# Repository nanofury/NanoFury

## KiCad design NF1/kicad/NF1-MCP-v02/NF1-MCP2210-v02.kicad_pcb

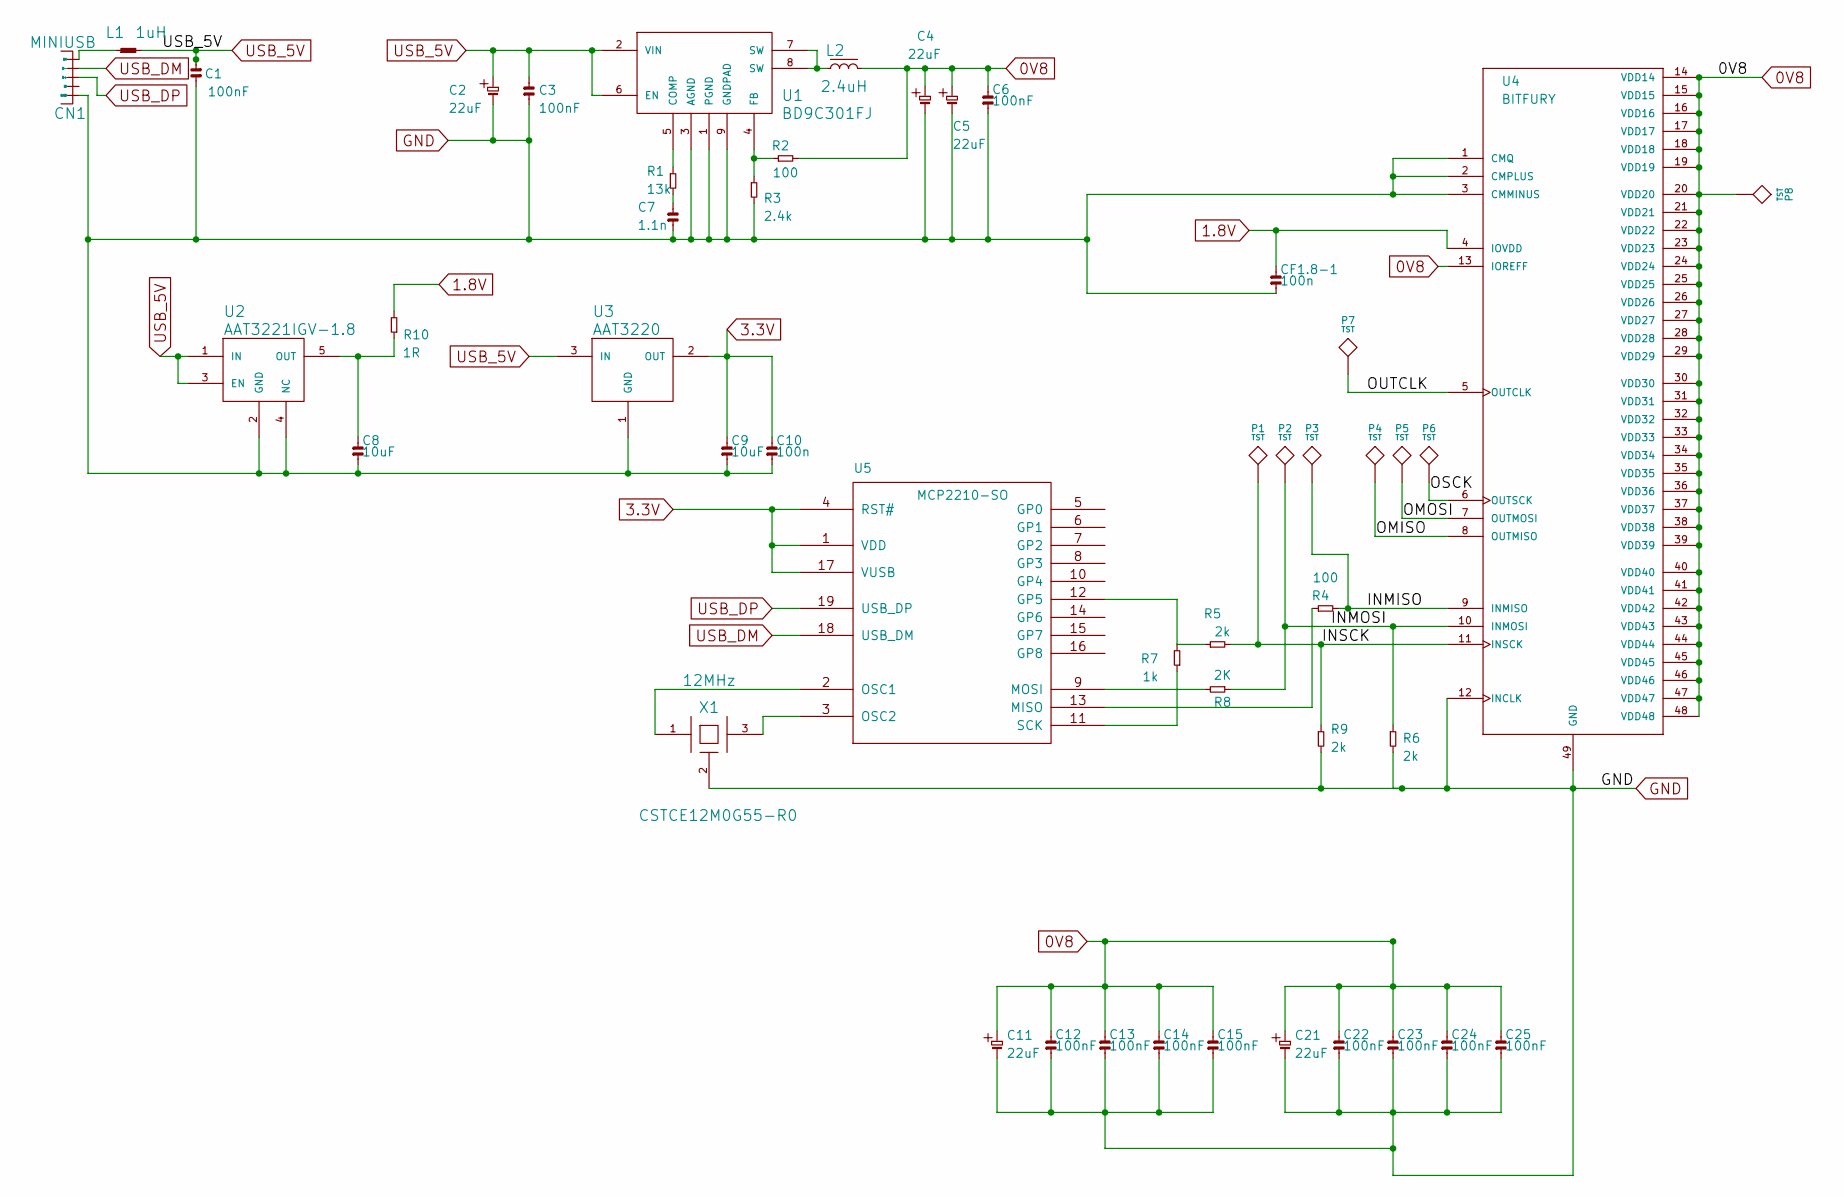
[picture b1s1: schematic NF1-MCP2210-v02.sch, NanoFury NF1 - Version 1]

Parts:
C1, C3, C6, C12, C13, C14, C15, C22, C23, C24, C25: 100nF; 0402
C2, C4, C5, C11, C21: 22uF; 0805
C7: 1.1n; 0402
C8, C9: 10uF; 0805
C10: 100n; 0402
CF1.8-1: 100n; 0402
CN1: MINIUSB; USBAPCB
L1: 1uH; 0402
L2: 2.4uH; 0630
P1, P2, P3, P4, P5, P6, P7, P8: TST; TP
R1: 13k; 0402
R2, R4: 100; 0402
R3: 2.4k; 0402
R5, R6, R9: 2k; 0402
R7: 1k; 0402
R8: 2K; 0402
R10: 1R; 0402
U1: BD9C301FJ; HTSOP-J8
U2: AAT3221IGV-1.8; SOT23-5
U3: AAT3220; SC59
U4: BITFURY; QFN48
U5: MCP2210-SO; SSOP-20
X1: 12MHz; CSTCE_G15C; Part Number CSTCE12M0G55-R0

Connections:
0V8: C4.1, C5.1, C6.1, C11.1, C12.1, C13.1, C14.1, C15.1, C21.1, C22.1, C23.1, C24.1, C25.1, L2.2, P8.1, R2.1, U4.13 (IOREFF), U4.14 (VDD14), U4.15 (VDD15), U4.16 (VDD16), U4.17 (VDD17), U4.18 (VDD18), U4.19 (VDD19), U4.20 (VDD20), U4.21 (VDD21), U4.22 (VDD22), U4.23 (VDD23), U4.24 (VDD24), U4.25 (VDD25), U4.26 (VDD26), U4.27 (VDD27), U4.28 (VDD28), U4.29 (VDD29), U4.30 (VDD30), U4.31 (VDD31), U4.32 (VDD32), U4.33 (VDD33), U4.34 (VDD34), U4.35 (VDD35), U4.36 (VDD36), U4.37 (VDD37), U4.38 (VDD38), U4.39 (VDD39), U4.40 (VDD40), U4.41 (VDD41), U4.42 (VDD42), U4.43 (VDD43), U4.44 (VDD44), U4.45 (VDD45), U4.46 (VDD46), U4.47 (VDD47), U4.48 (VDD48)
1.8V: CF1.8-1.1, R10.1, U4.4 (IOVDD)
3.3V: C9.1, C10.1, U3.2 (OUT), U5.1 (VDD), U5.4 (RST#), U5.17 (VUSB)
/INMISO: P3.1, R4.1, U4.9 (INMISO)
/INMOSI: P2.1, R6.2, R8.2, U4.10 (INMOSI)
/INSCK: P1.1, R5.1, R9.2, U4.11 (INSCK)
/OMISO: P4.1, U4.8 (OUTMISO)
/OMOSI: P5.1, U4.7 (OUTMOSI)
/OSCK: P6.1, U4.6 (OUTSCK)
/OUTCLK: P7.1, U4.5 (OUTCLK)
GND: C1.1, C2.2, C3.2, C4.2, C5.2, C6.2, C7.2, C8.2, C9.2, C10.2, C11.2, C12.2, C13.2, C14.2, C15.2, C21.2, C22.2, C23.2, C24.2, C25.2, CF1.8-1.2, CN1.5 (GND), R3.1, R6.1, R9.1, U1.1 (PGND), U1.3 (AGND), U1.9 (GNDPAD), U2.2 (GND), U2.4 (NC), U3.1 (GND), U4.1 (CMQ), U4.2 (CMPLUS), U4.3 (CMMINUS), U4.12 (INCLK), U4.49 (GND), X1.2 (GND)
unnamed: C7.1, R1.1
unnamed: R1.2, U1.5 (COMP)
unnamed: L2.1, U1.7 (SW), U1.8 (SW)
unnamed: R2.2, R3.2, U1.4 (FB)
unnamed: R7.2, U5.11 (SCK)
unnamed: R4.2, U5.13 (MISO)
unnamed: R8.1, U5.9 (MOSI)
unnamed: R5.2, R7.1, U5.12 (GP5)
unnamed: U5.2 (OSC1), X1.1
unnamed: U5.3 (OSC2), X1.3
unnamed: CN1.1 (5V), L1.1
unnamed: C8.1, R10.2, U2.5 (OUT)
USB_5V: C1.2, C2.1, C3.1, L1.2, U1.2 (VIN), U1.6 (EN), U2.1 (IN), U2.3 (EN), U3.3 (IN)
USB_DM: CN1.2 (D-), U5.18 (USB_DM)
USB_DP: CN1.3 (D+), U5.19 (USB_DP)

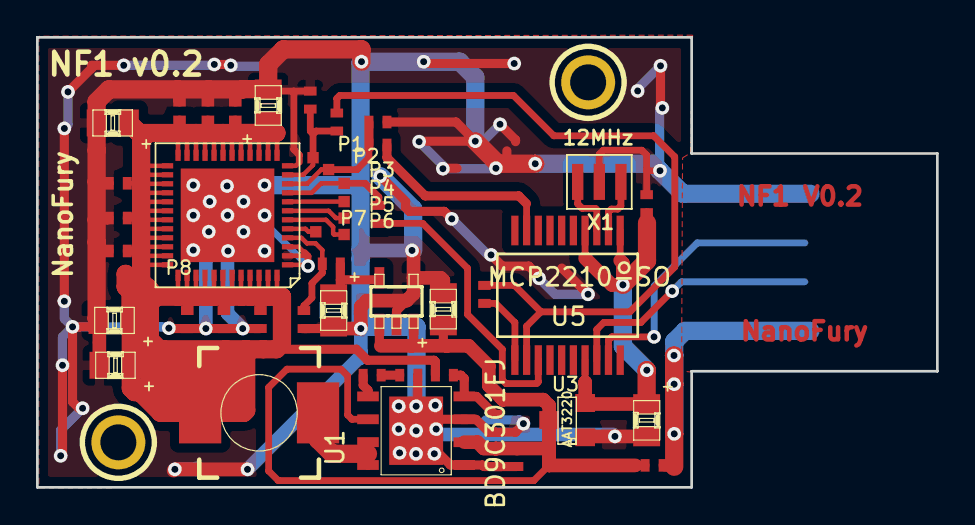
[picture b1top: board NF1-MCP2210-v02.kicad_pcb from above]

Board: 2 copper layers, 50.0 x 25.0 mm, 50 parts (1 on the bottom side), 26 nets.

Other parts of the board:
Hole2mm, Hole2mm1: P***; Hole2mm

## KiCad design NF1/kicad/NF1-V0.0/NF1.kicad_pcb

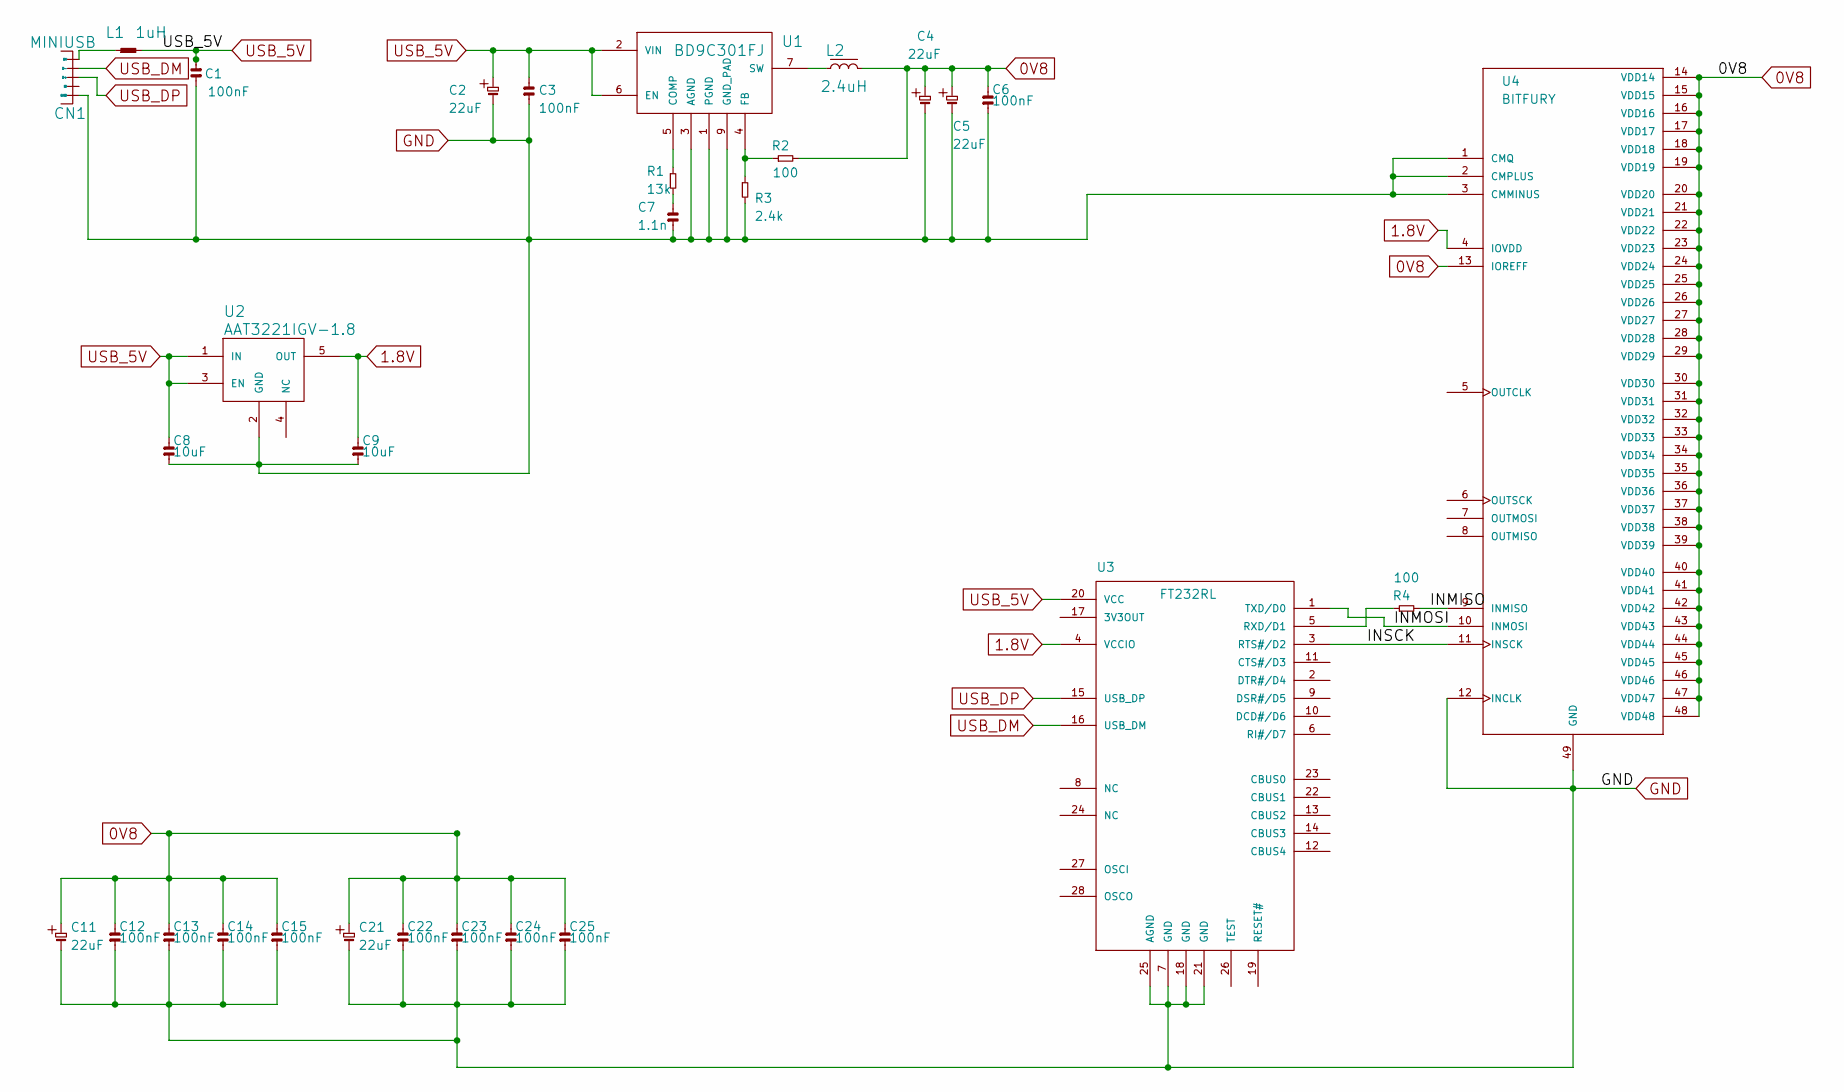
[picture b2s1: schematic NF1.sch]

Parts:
C1, C3, C6, C12, C13, C14, C15, C22, C23, C24, C25: 100nF; 0402
C2, C4, C5, C11, C21: 22uF; 0805
C7: 1.1n; 0402
C8, C9: 10uF; 0805
CN1: MINIUSB; USBAPCB
L1: 1uH; 0402
L2: 2.4uH; 0630
R1: 13k; 0402
R2, R4: 100; 0402
R3: 2.4k; 0402
U1: BD9C301FJ; HTSOP-J8
U2: AAT3221IGV-1.8; SOT23-5
U3: FT232RL; SSOP28
U4: BITFURY; QFN48

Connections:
0V8: C4.1, C5.1, C6.1, C11.1, C12.1, C13.1, C14.1, C15.1, C21.1, C22.1, C23.1, C24.1, C25.1, L2.2, R2.1, U4.13 (IOREFF), U4.14 (VDD14), U4.15 (VDD15), U4.16 (VDD16), U4.17 (VDD17), U4.18 (VDD18), U4.19 (VDD19), U4.20 (VDD20), U4.21 (VDD21), U4.22 (VDD22), U4.23 (VDD23), U4.24 (VDD24), U4.25 (VDD25), U4.26 (VDD26), U4.27 (VDD27), U4.28 (VDD28), U4.29 (VDD29), U4.30 (VDD30), U4.31 (VDD31), U4.32 (VDD32), U4.33 (VDD33), U4.34 (VDD34), U4.35 (VDD35), U4.36 (VDD36), U4.37 (VDD37), U4.38 (VDD38), U4.39 (VDD39), U4.40 (VDD40), U4.41 (VDD41), U4.42 (VDD42), U4.43 (VDD43), U4.44 (VDD44), U4.45 (VDD45), U4.46 (VDD46), U4.47 (VDD47), U4.48 (VDD48)
1.8V: C9.1, U2.5 (OUT), U3.4 (VCCIO), U4.4 (IOVDD)
/INMISO: R4.1, U4.9 (INMISO)
/INMOSI: U3.1 (TXD/D0), U4.10 (INMOSI)
/INSCK: U3.3 (RTS#/D2), U4.11 (INSCK)
GND: C1.1, C2.2, C3.2, C4.2, C5.2, C6.2, C7.2, C8.2, C9.2, C11.2, C12.2, C13.2, C14.2, C15.2, C21.2, C22.2, C23.2, C24.2, C25.2, CN1.5 (GND), R3.1, U1.1 (PGND), U1.3 (AGND), U1.9 (GND_PAD), U2.2 (GND), U3.7 (GND), U3.18 (GND), U3.21 (GND), U3.25 (AGND), U4.1 (CMQ), U4.2 (CMPLUS), U4.3 (CMMINUS), U4.12 (INCLK), U4.49 (GND)
unnamed: R2.2, R3.2, U1.4 (FB)
unnamed: C7.1, R1.1
unnamed: R1.2, U1.5 (COMP)
unnamed: R4.2, U3.5 (RXD/D1)
unnamed: L2.1, U1.7 (SW)
unnamed: CN1.1 (5V), L1.1
USB_5V: C1.2, C2.1, C3.1, C8.1, L1.2, U1.2 (VIN), U1.6 (EN), U2.1 (IN), U2.3 (EN), U3.20 (VCC)
USB_DM: CN1.2 (D-), U3.16 (USB_DM)
USB_DP: CN1.3 (D+), U3.15 (USB_DP)

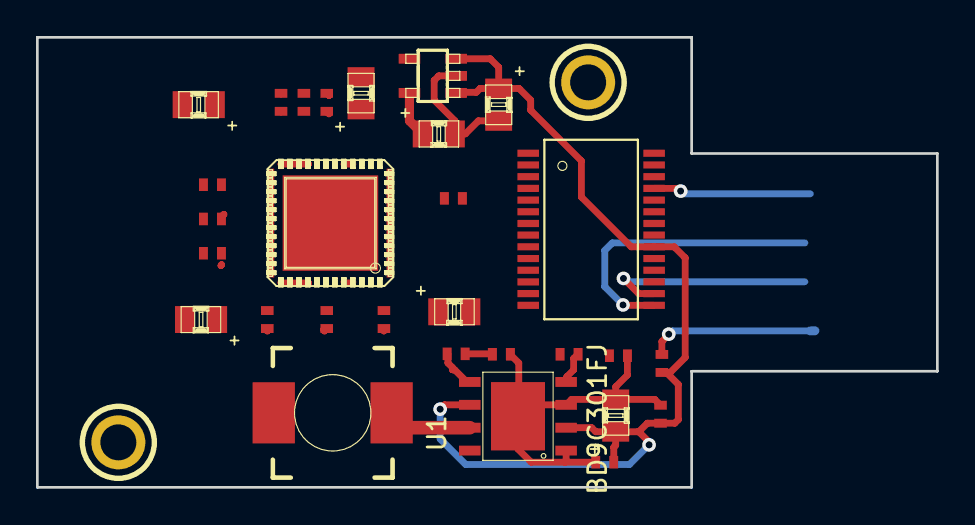
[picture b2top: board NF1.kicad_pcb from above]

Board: 2 copper layers, 50.0 x 25.0 mm, 32 parts (1 on the bottom side), 15 nets.

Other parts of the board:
Hole2mm, Hole2mm1: P***; Hole2mm

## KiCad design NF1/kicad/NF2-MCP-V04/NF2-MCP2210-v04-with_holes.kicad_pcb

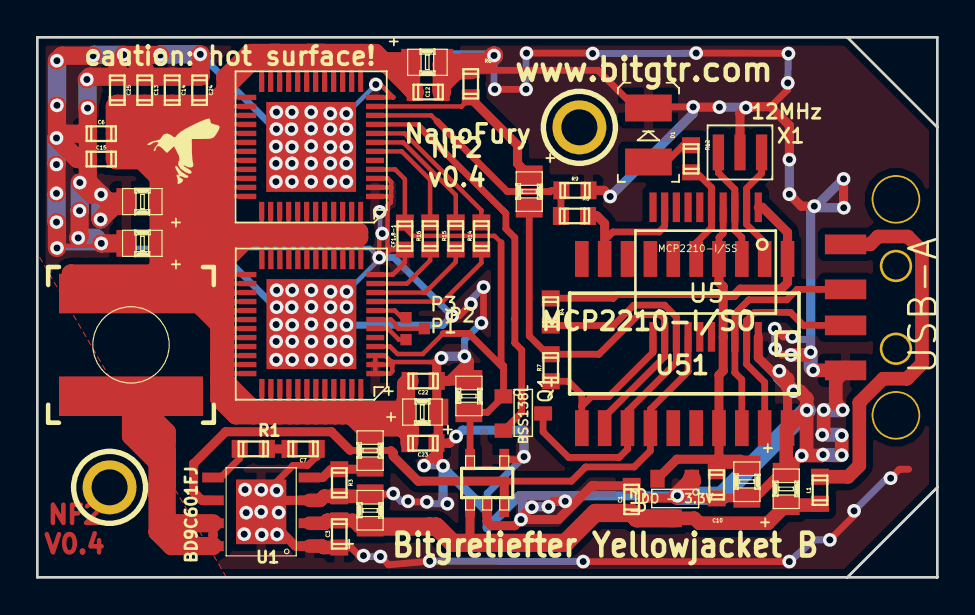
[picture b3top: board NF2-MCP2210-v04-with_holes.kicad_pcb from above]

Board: 2 copper layers, 50.0 x 30.0 mm, 53 parts (0 on the bottom side), 33 nets.

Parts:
C1, C3, C6, C12, C13, C14, C15, C22, C23, C24, C25: 100nF; 0603
C2: 22uF/10V; 0805
C4, C5, C11, C21: 22uF; 0805
C7: 1.1n; 0603
C8, C9: 4.7uF/4V; 0805
C10: 100n; 0603
CF1: 22uF/10V; 0805
CF1.8-1: 100n; 0603
CN1: USB-A; CNC-1001-011-01101
D1: LED; 2PLCC
Hole2mm, Hole2mm1: P***; Hole2mm
L1: 10R@100MHz; 0603
L2: 1.0uH; SRN8040
P1, P2, P3: TST; TP
Q1: BSS138L; SOT23
R1: 5.6k; 0603
R2: 180; 0805
R3: 2.4k; 0603
R4, R6, R9: 2k; 0603
R5: 2k; 0805
R7, R12: 1k; 0603
R8: 2K; 0603
R14, R15, R16: 0R; 0603
U1: BD9C601FJ; HTSOP-J8
U2: LDO - 1.8V; SOT23-5
U3: LDO - 3.3V; SOT23
U4, U6: BITFURY; QFN48
U5: MCP2210-I/SS; SSOP-20
U51: MCP2210-I/SO; SOIC20
X1: 12MHz; CSTCE_G15C

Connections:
0V8: C4.1, C5.1, C6.1, C11.1, C12.1, C13.1, C14.1, C15.1, C21.1, C22.1, C23.1, C24.1, C25.1, L2.2, R2.1, U4.13, U4.14, U4.15, U4.16, U4.17, U4.18, U4.19, U4.20, U4.21, U4.22, U4.23, U4.24, U4.25, U4.26, U4.27, U4.28, U4.29, U4.30, U4.31, U4.32, U4.33, U4.34, U4.35, U4.36, U4.37, U4.38, U4.39, U4.40, U4.41, U4.42, U4.43, U4.44, U4.45, U4.46, U4.47, U4.48, U6.13, U6.14, U6.15, U6.16, U6.17, U6.18, U6.19, U6.20, U6.21, U6.22, U6.23, U6.24, U6.25, U6.26, U6.27, U6.28, U6.29, U6.30, U6.31, U6.32, U6.33, U6.34, U6.35, U6.36, U6.37, U6.38, U6.39, U6.40, U6.41, U6.42, U6.43, U6.44, U6.45, U6.46, U6.47, U6.48
1.8V: C8.1, CF1.8-1.1, Q1.1, U2.5, U4.4, U6.4
3.3V: C9.1, C10.1, R4.2, U3.2, U5.1, U5.4, U5.17, U51.1, U51.4, U51.17
/LED: R12.2, U5.5, U51.5
/MISO: Q1.3, R4.1, U5.13, U51.13
/MOSI: R8.1, U5.9, U51.9
/OMISO2: P3.1, U6.8
/OMOSI2: P2.1, U6.7
/OSC1: U5.2, U51.2, X1.1
/OSC2: U5.3, U51.3, X1.3
/OSCK2: P1.1, U6.6
/SCK: R7.2, U5.11, U51.11
/SCK_OVR: R5.2, R7.1, U5.12, U51.12
GND: C1.1, C2.2, C3.2, C4.2, C5.2, C6.2, C7.2, C8.2, C9.2, C10.2, C11.2, C12.2, C13.2, C14.2, C15.2, C21.2, C22.2, C23.2, C24.2, C25.2, CF1.2, CF1.8-1.2, CN1.5, D1.2, R3.1, R6.1, R9.1, U1.1, U1.3, U1.9, U2.2, U2.4, U3.1, U4.1, U4.2, U4.3, U4.12, U4.49, U5.20, U6.1, U6.2, U6.3, U6.12, U6.49, U51.20, X1.2
INMISO: Q1.2, U4.9
INMOSI: R8.2, R9.2, U4.10
INSCK: R5.1, R6.2, U4.11
unnamed: R2.2, R3.2, U1.4
unnamed: CN1.1, L1.1
unnamed: R1.2, U1.5
unnamed: C7.1, R1.1
unnamed: R14.2, U6.9
unnamed: R15.2, U6.10
unnamed: R16.2, U6.11
unnamed: L2.1, U1.7, U1.8
unnamed: D1.1, R12.1
OUTMISO1: R14.1, U4.8
OUTMOSI1: R15.1, U4.7
OUTSCK1: R16.1, U4.6
USB_5V: C1.2, C2.1, C3.1, CF1.1, L1.2, U1.2, U2.1, U3.3
USB_DM: CN1.2, U5.18, U51.18
USB_DP: CN1.3, U5.19, U51.19
V_EN: U1.6, U2.3, U5.14, U51.14
